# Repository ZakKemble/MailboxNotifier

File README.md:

Remote Mail Notifier (and GPS tracker)
======================================

A notifier for when mail is received in your mail box! Uses an A9G GPRS/GPS module to send HTTP requests to a web server via the mobile network.\
A PHP script then sends messages to a Telegram group chat using the bot API. Since the A9G also has a built-in GPS receiver the mail notifier can be used as a GPS tracker!\
Also incorporates a BME280 environmental sensor and should last for around 4-5 years on a single charge of a 10440 lithium battery (~320mAh, equivalent AAA size), if mail is received 3 times per week.

[https://blog.zakkemble.net/remote-mail-notifier-and-gps-tracker/](https://blog.zakkemble.net/remote-mail-notifier-and-gps-tracker/)

--------

Zak Kemble

contact@zakkemble.net

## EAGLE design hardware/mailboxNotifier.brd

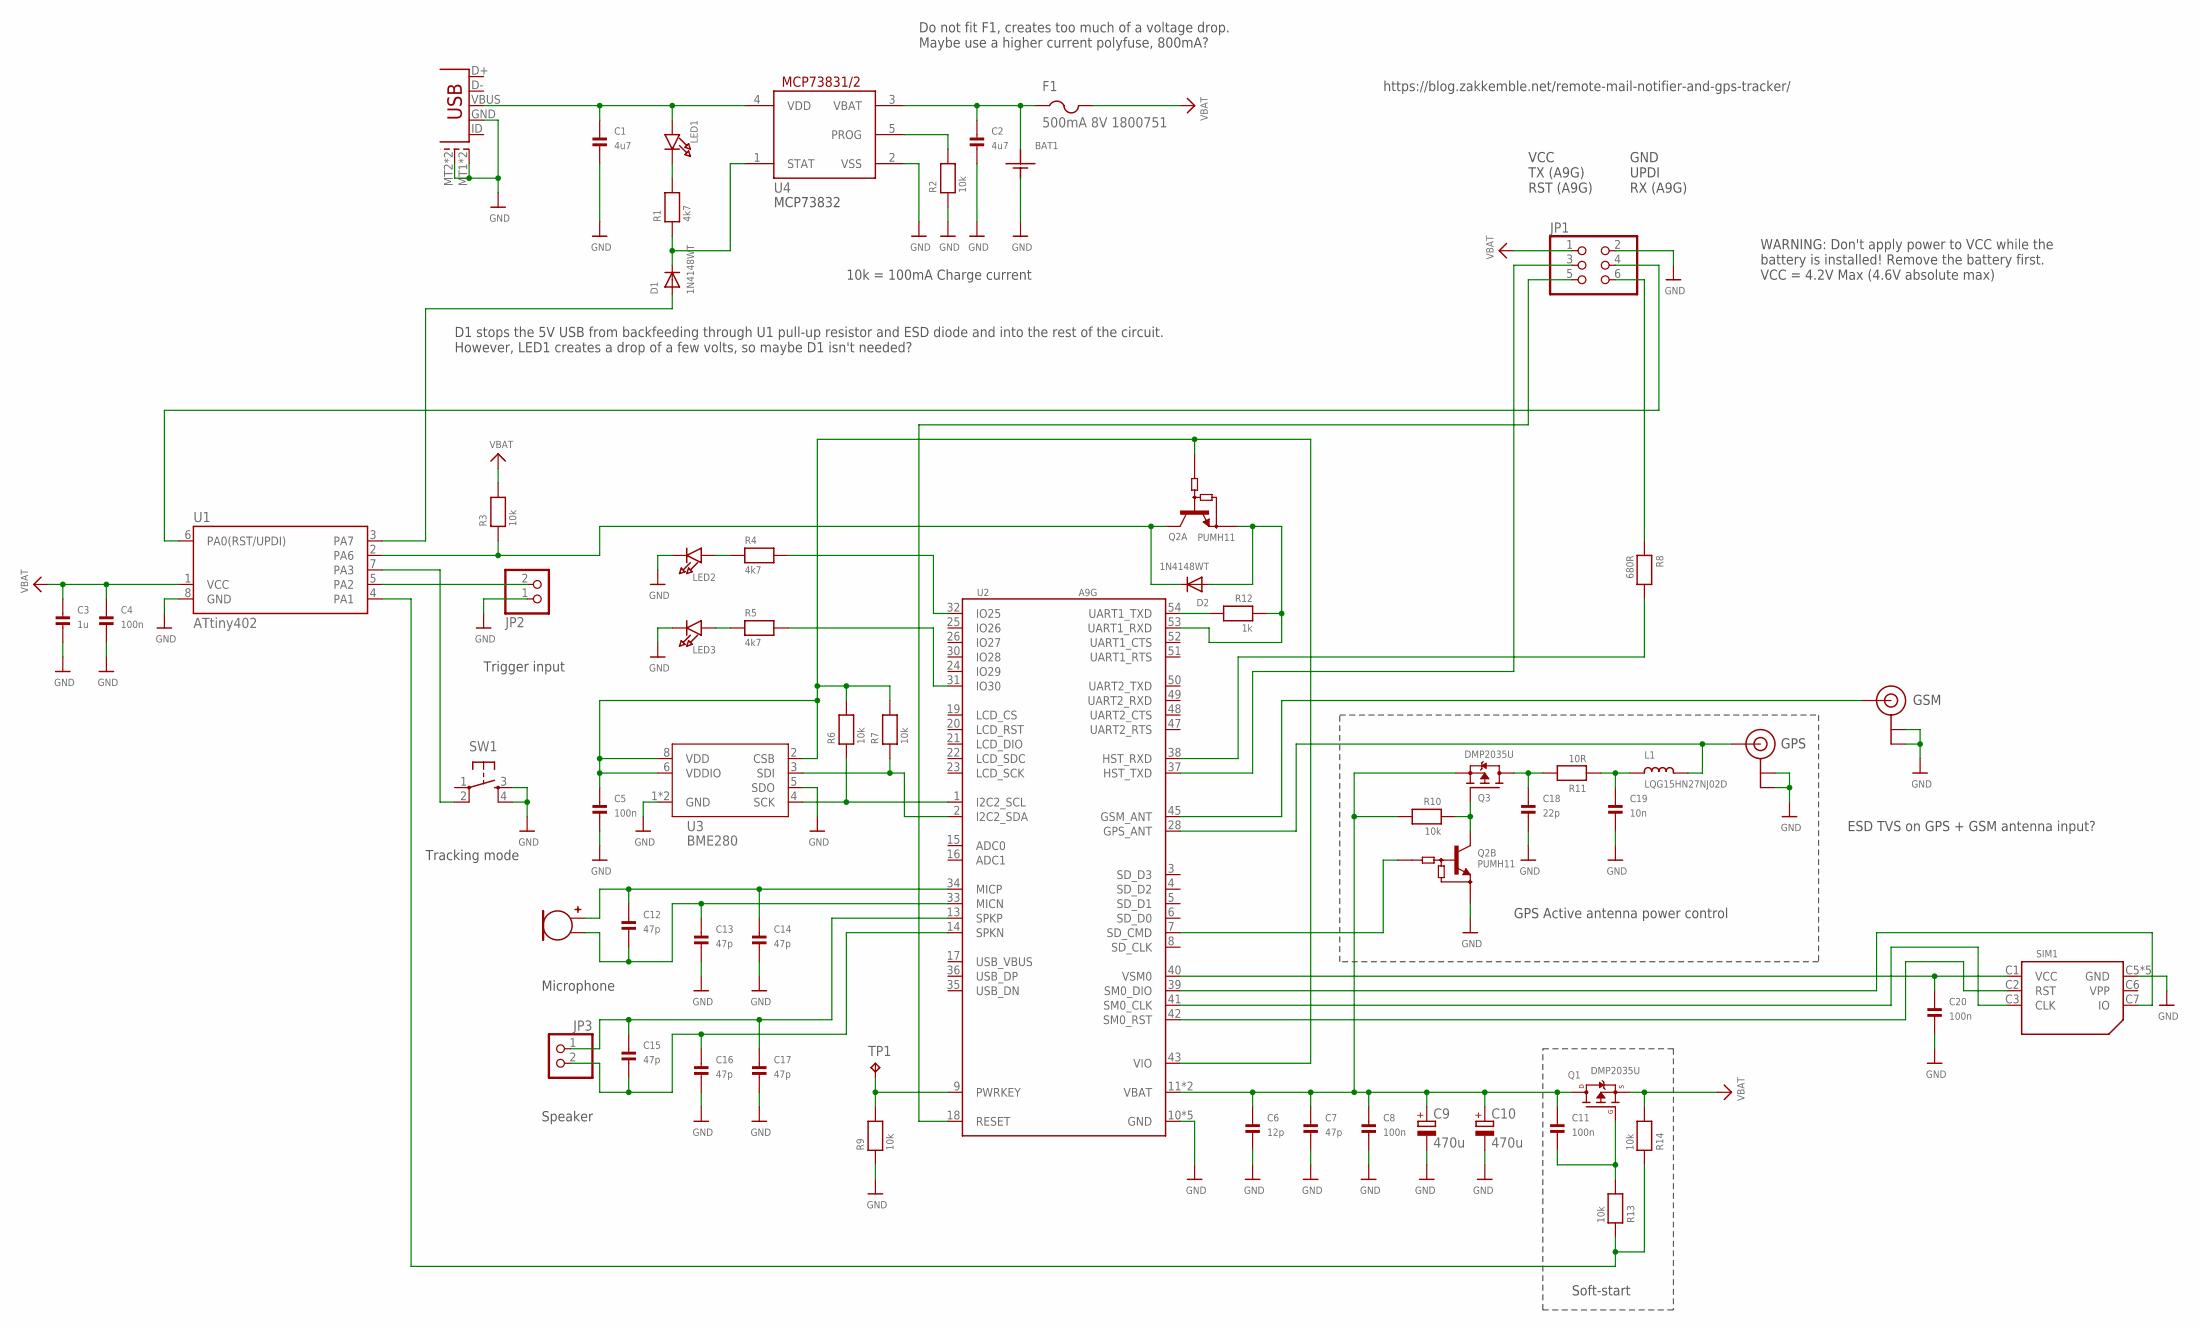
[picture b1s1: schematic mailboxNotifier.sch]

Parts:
BAT1: BATTERY_HOLDER1XAAA_PCB; BATT_HOLDER_AAA_PCB
C1, C2: 4u7; 0805_NO_OUTLINE
C3: 1u; _0603MP
C4, C5, C8, C11, C20: 100n; 0402_SMALL
C6: 12p; 0402_SMALL
C7, C12, C13, C14, C15, C16, C17: 47p; 0402_SMALL
C9, C10: 470u; E2,5-6
C18: 22p; 0402_SMALL
C19: 10n; 0402_SMALL
D1, D2: 1N4148WT; SOD-523
F1: 500mA 8V 1800751; 1206
JP1: PINHD-2X3; 2X03
JP2: PINHD-1X2/90; 1X02/90
JP3: PINHD-1X2; 1X02
L1: LQG15HN27NJ02D; 0402_SMALL
LED1, LED2, LED3: LED0603_NOOUTLINE; CHIPLED_0603_NOOUTLINE
MIC1: MIC6MM_RA_SWAP
Q1: DMP2035U; SOT-23-WIDE
Q2: PUMH11; SOT-363
Q3: DMP2035U; SOT23-R
R1, R4, R5: 4k7; 0402_SMALL
R2, R3, R6, R7, R9, R10, R13, R14: 10k; 0402_SMALL
R8: 680R; 0402_SMALL
R11: 10R; 0402_SMALL
R12: 1k; 0402_SMALL
SIM1: SIMCARDSOCKET; SIM_SOCKET1
SW1: SPST_TACTG75_3X4; TACT_SMD5
TP1: TPTP10R; TP10R
U1: ATtiny402; SOIC8_150MIL_SMPAD
U2: A9G
U3: BME280
U4: MCP73831/OT; SOT23-5L
U$38, U$55: U.FL
USB1: USB-MICROBSAFEBEE; USB-MICROB_SAFEBEE

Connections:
GND: BAT1.NEG, C1.2, C2.2, C3.2, C4.2, C5.2, C6.2, C7.2, C8.2, C9.-, C10.-, C13.2, C14.2, C16.2, C17.2, C18.2, C19.2, C20.2, JP1.2, JP2.1, LED2.C, LED3.C, Q2.4 (E), R2.1, R9.1, SIM1.C5 (GND), SIM1.GND1 (GND), SIM1.GND2 (GND), SIM1.GND3 (GND), SIM1.GND4 (GND), SW1.3 (S), SW1.4 (S1), U1.8 (GND), U2.10 (GND), U2.27 (GND), U2.29 (GND), U2.44 (GND), U2.46 (GND), U3.1 (GND), U3.5 (SDO), U3.7 (GND), U4.2 (VSS), U$38.1 (GND), U$38.2 (GND), U$55.1 (GND), U$55.2 (GND), USB1.GND, USB1.MT1 (SHEILD1), USB1.MT2 (SHEILD2), USB1.MT3 (SHEILD1), USB1.MT4 (SHEILD2)
unnamed: SIM1.C3 (CLK), U2.41 (SM0_CLK)
unnamed: LED1.C, R1.2
unnamed: SIM1.C2 (RST), U2.42 (SM0_RST)
unnamed: JP1.4, U1.6 (PA0(RST/UPDI))
unnamed: R2.2, U4.5 (PROG)
unnamed: JP1.5, U2.18 (RESET)
unnamed: D2.A, Q2.1 (E), R12.1, U2.53 (UART1_RXD)
unnamed: R12.2, U2.54 (UART1_TXD)
unnamed: D1.A, U1.3 (PA7)
unnamed: D2.K (C), Q2.6 (C), R3.1, U1.2 (PA6)
unnamed: C5.1, Q2.2 (B), R6.2, R7.2, U2.43 (VIO), U3.2 (CSB), U3.6 (VDDIO), U3.8 (VDD)
unnamed: JP2.2, U1.5 (PA2)
unnamed: C20.1, SIM1.C1 (VCC), U2.40 (VSM0)
unnamed: SW1.2 (P1), U1.7 (PA3)
unnamed: R9.2, TP1.TP, U2.9 (PWRKEY)
unnamed: SIM1.C7 (IO), U2.39 (SM0_DIO)
unnamed: Q2.3 (C), Q3.1 (G), R10.1
unnamed: U2.45 (GSM_ANT), U$55.3 (SIGNAL)
unnamed: R4.2, U2.32 (IO25)
unnamed: R6.1, U2.1 (I2C2_SCL), U3.4 (SCK)
unnamed: R5.2, U2.31 (IO30)
unnamed: C12.1, C14.1, MIC1.POS, U2.34 (MICP)
unnamed: Q2.5 (B), U2.7 (SD_CMD)
unnamed: R8.2, U2.38 (HST_RXD)
unnamed: R7.1, U2.2 (I2C2_SDA), U3.3 (SDI)
unnamed: JP1.3, U2.37 (HST_TXD)
unnamed: BAT1.POS, C2.1, F1.1, U4.3 (VBAT)
unnamed: JP1.6, R8.1
unnamed: L1.2, U2.28 (GPS_ANT), U$38.3 (SIGNAL)
unnamed: LED3.A, R5.1
unnamed: C1.1, LED1.A, U4.4 (VDD), USB1.VBUS
unnamed: R13.1, R14.1, U1.4 (PA1)
unnamed: D1.K (C), R1.1, U4.1 (STAT)
unnamed: C18.1, Q3.3 (D), R11.2
unnamed: C19.1, L1.1, R11.1
unnamed: C12.2, C13.1, MIC1.NEG, U2.33 (MICN)
unnamed: C15.1, C17.1, JP3.1, U2.13 (SPKP)
unnamed: LED2.A, R4.1
unnamed: C11.2, Q1.1 (G), R13.2
unnamed: C15.2, C16.1, JP3.2, U2.14 (SPKN)
unnamed: C6.1, C7.1, C8.1, C9.+, C10.+, C11.1, Q1.3 (D), Q3.2 (S), R10.2, U2.11 (VBAT), U2.12 (VBAT)
VBAT: C3.1, C4.1, F1.2, JP1.1, Q1.2 (S), R3.2, R14.2, U1.1 (VCC)

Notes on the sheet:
MCP73832
ESD TVS on GPS + GSM antenna input?
WARNING: Don't apply power to VCC while the battery is installed! Remove the battery first. VCC = 4.2V Max (4.6V absolute max)
VCC TX (A9G) RST (A9G)
GND UPDI RX (A9G)
10k = 100mA Charge current
D1 stops the 5V USB from backfeeding through U1 pull-up resistor and ESD diode and into the rest of the circuit. However, LED1 creates a drop of a few volts, so maybe D1 isn't needed?
Do not fit F1, creates too much of a voltage drop. Maybe use a higher current polyfuse, 800mA?
GPS Active antenna power control
Soft-start
GSM
GPS
Speaker
Microphone
Tracking mode
Trigger input
https://blog.zakkemble.net/remote-mail-notifier-and-gps-tracker/

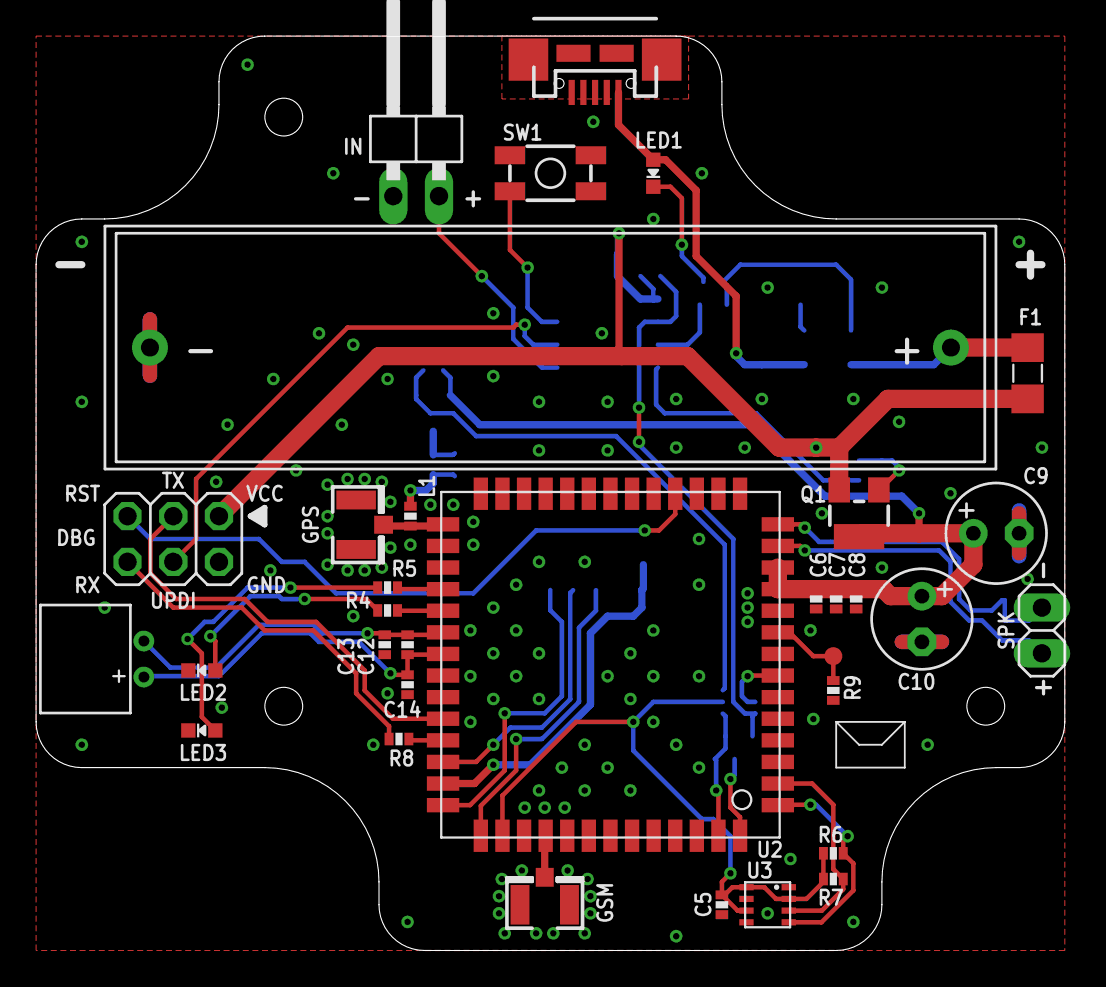
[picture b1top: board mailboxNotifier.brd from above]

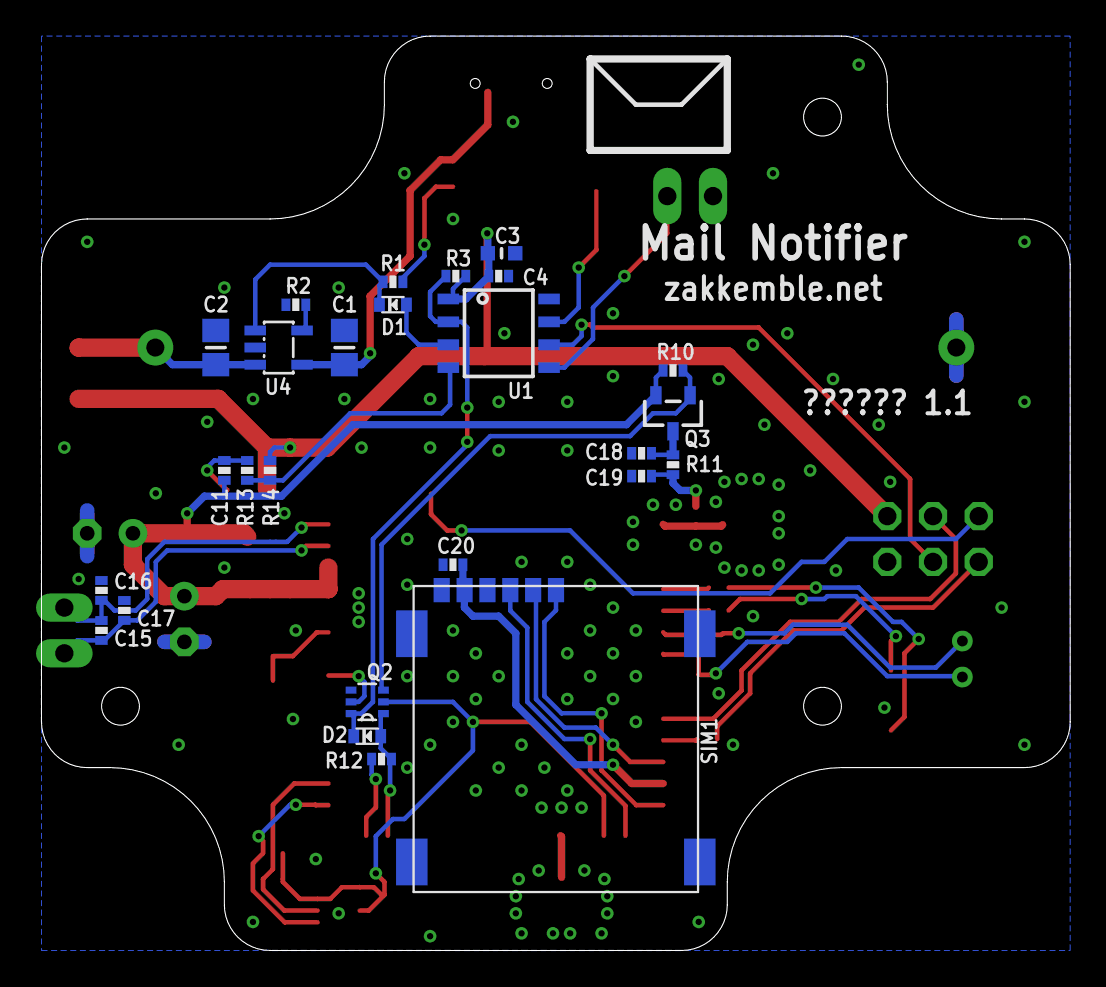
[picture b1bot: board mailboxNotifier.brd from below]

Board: 2 copper layers, 57.1 x 50.8 mm, 59 parts (26 on the bottom side), 43 nets.

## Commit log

2020-01-06 Initial commit :hurtrealbad:
2020-05-17 Fixes and tweaks
    Various fixes and tweaks, like default clock source is 20MHz, not 16MHz!

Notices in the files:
parts and their libraries:
microbuilder: This work is placed in the public domain, and may be freely used for commercial and non-commercial work with the following conditions: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
